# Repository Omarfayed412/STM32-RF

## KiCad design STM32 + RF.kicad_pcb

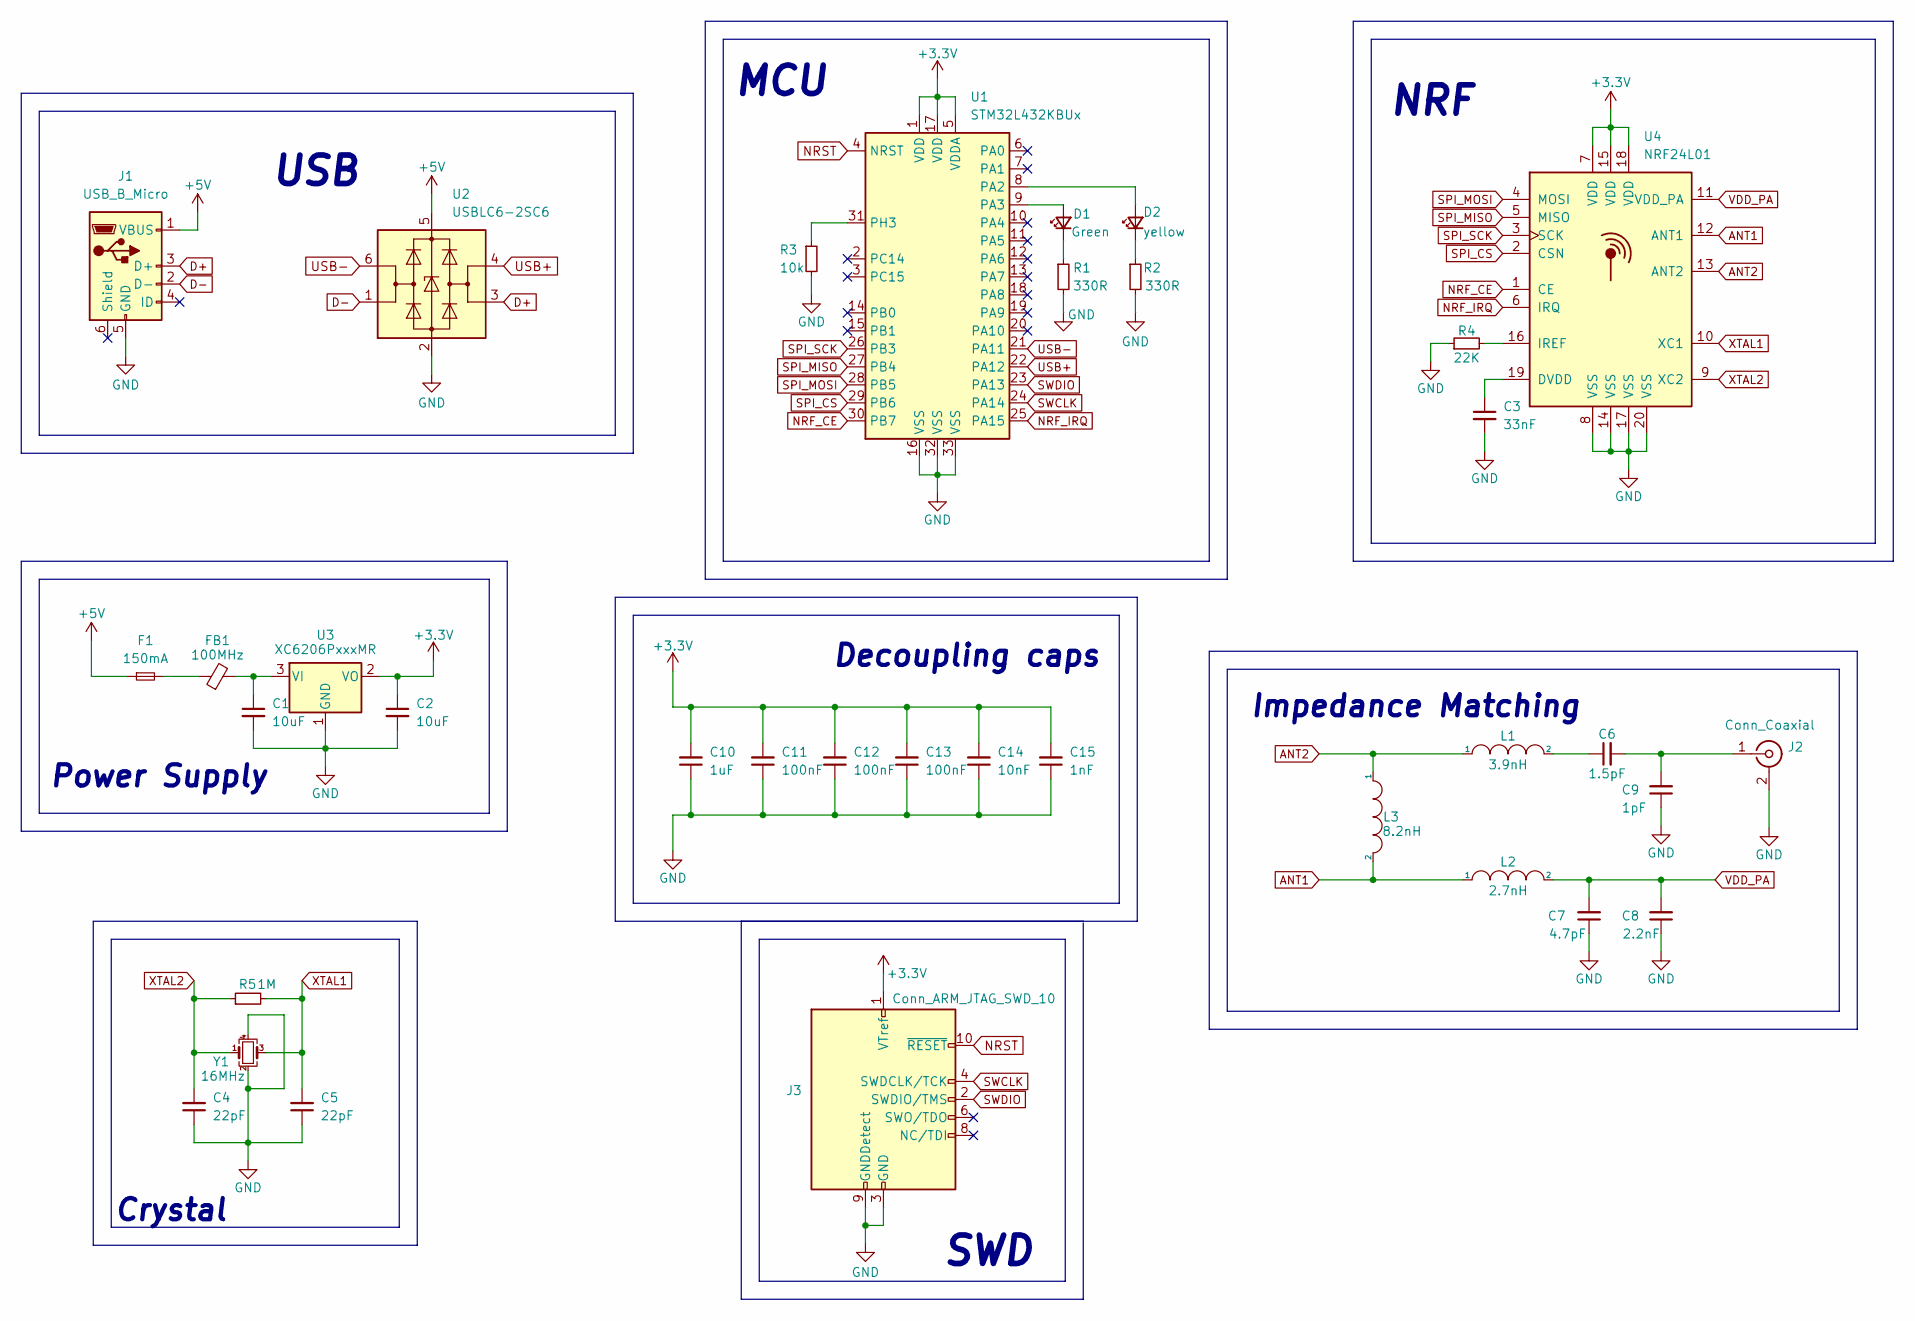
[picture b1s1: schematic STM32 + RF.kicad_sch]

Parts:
C1, C2: 10uF; C_0603_1608Metric
C3: 33nF; C_0402_1005Metric
C4, C5: 22pF; C_0402_1005Metric
C6: 1.5pF; C_0402_1005Metric
C7: 4.7pF; C_0402_1005Metric
C8: 2.2nF; C_0402_1005Metric
C9: 1pF; C_0402_1005Metric
C10: 1uF; C_0402_1005Metric_Pad0.74x0.62mm_HandSolder
C11, C12, C13: 100nF; C_0402_1005Metric_Pad0.74x0.62mm_HandSolder
C14: 10nF; C_0402_1005Metric_Pad0.74x0.62mm_HandSolder
C15: 1nF; C_0402_1005Metric_Pad0.74x0.62mm_HandSolder
D1: Green; LED_0603_1608Metric
D2: yellow; LED_0603_1608Metric
F1: 150mA; Fuse_1210_3225Metric
FB1: 100MHz; L_0805_2012Metric
J1: USB_B_Micro; USB_Micro-B_Molex_47346-0001
J2: Conn_Coaxial; LINX_CONSMA013.031-G
J3: Conn_ARM_JTAG_SWD_10; PinHeader_2x05_P1.27mm_Vertical
L1: 3.9nH; L_0402_1005Metric
L2: 2.7nH; L_0402_1005Metric
L3: 8.2nH; L_0402_1005Metric
R1, R2: 330R; R_0603_1608Metric
R3: 10k; R_0603_1608Metric
R4: 22K; R_0402_1005Metric
R5: 1M; R_0402_1005Metric
U1: STM32L432KBUx; QFN-32-1EP_5x5mm_P0.5mm_EP3.45x3.45mm
U2: USBLC6-2SC6; SOT-23-6
U3: XC6206PxxxMR; SOT-23
U4: NRF24L01; QFN-20-1EP_4x4mm_P0.5mm_EP2.5x2.5mm
Y1: 16MHz; Crystal_SMD_0603-4Pin_6.0x3.5mm

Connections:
+3.3V: C2.1, C10.2, C11.2, C12.2, C13.2, C14.2, C15.2, J3.1 (VTref), U1.1 (VDD), U1.5 (VDDA), U1.17 (VDD), U3.2 (VO), U4.7 (VDD), U4.15 (VDD), U4.18 (VDD)
+5V: F1.1, J1.1 (VBUS), U2.5 (VBUS)
ANT1: L2.1, L3.2, U4.12 (ANT1)
ANT2: L1.1, L3.1, U4.13 (ANT2)
D+: J1.3 (D+), U2.3 (I/O2)
D-: J1.2 (D-), U2.1 (I/O1)
GND: C1.2, C2.2, C3.2, C4.1, C5.1, C7.1, C8.1, C9.1, C10.1, C11.1, C12.1, C13.1, C14.1, C15.1, J1.5 (GND), J2.2 (Ext), J3.3 (GND), J3.5 (GND), J3.9 (GNDDetect), R1.2, R2.2, R3.2, R4.1, U1.16 (VSS), U1.32 (VSS), U1.33 (VSS), U2.2 (GND), U3.1 (GND), U4.8 (VSS), U4.14 (VSS), U4.17 (VSS), U4.20 (VSS), U4.21, Y1.2, Y1.4
NRF_CE: U1.30 (PB7), U4.1 (CE)
NRF_IRQ: U1.25 (PA15), U4.6 (IRQ)
NRST: J3.10 (~RESET), U1.4 (NRST)
unnamed: C1.1, FB1.2, U3.3 (VI)
unnamed: C3.1, U4.19 (DVDD)
unnamed: C6.1, L1.2
unnamed: C6.2, C9.2, J2.1 (In)
unnamed: D1.1 (K), R1.1
unnamed: D1.2 (A), U1.9 (PA3)
unnamed: D2.1 (K), R2.1
unnamed: D2.2 (A), U1.8 (PA2)
unnamed: F1.2, FB1.1
unnamed: R3.1, U1.31 (PH3)
unnamed: R4.2, U4.16 (IREF)
SPI_CS: U1.29 (PB6), U4.2 (CSN)
SPI_MISO: U1.27 (PB4), U4.5 (MISO)
SPI_MOSI: U1.28 (PB5), U4.4 (MOSI)
SPI_SCK: U1.26 (PB3), U4.3 (SCK)
SWCLK: J3.4 (SWDCLK/TCK), U1.24 (PA14)
SWDIO: J3.2 (SWDIO/TMS), U1.23 (PA13)
USB+: U1.22 (PA12), U2.4 (I/O2)
USB-: U1.21 (PA11), U2.6 (I/O1)
VDD_PA: C7.2, C8.2, L2.2, U4.11 (VDD_PA)
XTAL1: C5.2, R5.2, U4.10 (XC1), Y1.3
XTAL2: C4.2, R5.1, U4.9 (XC2), Y1.1

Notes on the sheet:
Decoupling caps
Crystal
SWD
Impedance Matching
USB
Power Supply
MCU
NRF

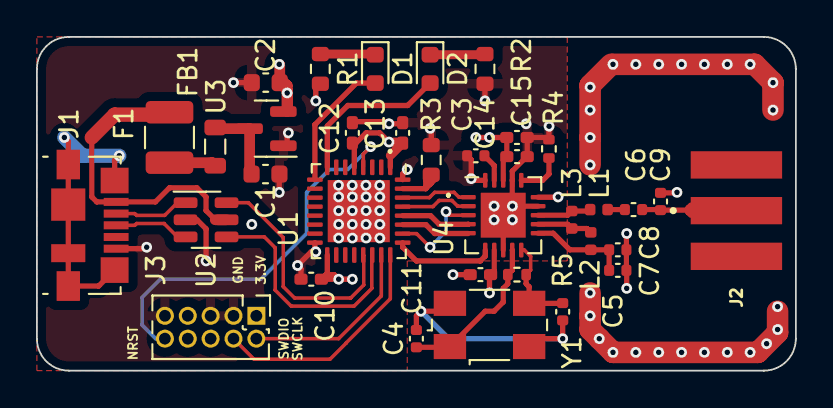
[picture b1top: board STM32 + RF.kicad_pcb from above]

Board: 4 copper layers, 42.2 x 18.5 mm, 35 parts (0 on the bottom side), 32 nets.

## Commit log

2023-11-23 Added the design files for Kicad
